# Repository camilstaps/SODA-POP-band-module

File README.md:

# SODA POP band module
This repository contains Eagle files for band modules for the
[SODA POP][sodapop] by [Steve Weber KD1JV][kd1jv]. The SODA POP was originally
designed as a single band QRP CW transceiver on a 3.6" square board. The mods
described below make it a multi-bander.

**Warning**: I have not actually tried to use these files yet. They may have
errors. I shall in no event be liable for any claim, damages or other
liability, whether in action of contract, tort or otherwise, arising from, out
of or in connection with these files or their use.

Two versions are available: one with headers and either through-hole or SMT
components; one with SMT components and a DB9 connector. The DB9 one has an
option for automatic band selection. Some modifications have to be made to the
main board for both modules.

The most recent version of these modules can be ordered from OSH Park from
https://oshpark.com/profiles/PD7LOL.

---

- [Common mods](#common-mods)
- [Through-hole / SMT module with headers](#through-hole--smt-module-with-headers)
- [SMT module with DB9 connector](#smt-module-with-db9-connector)
- [SMT module with DB9 connector and auto band selection](#smt-module-with-db9-connector-and-auto-band-selection)
- [Horizontal format SMT module with DB9 connector and auto band selection](#horizontal-format-smt-module-with-db9-connector-and-auto-band-selection)
- [Author &amp; license](#author--license)

---

## Common mods

### Main board
- The following components are moved to the band module:
	- **TX**: C2, C3, C5 (and C6), C12, L7, L8
	- **RX**: L3, CT1, C31, CT2, L4

	Their values can be taken from the manual under "Band specific parts". One
	part, C31, is on the band module even though it has a fixed value (5p).

### Software
- The software has to be adapted as described in the manual under "Manual band
  selection".

## Through-hole / SMT module With headers
- L3 has to be shorted (on the main board).
- Add 2-pin female headers on the place of L7 and L8
- Add 3-pin female headers on the place of CT1 and CT2 (middle pin should be
  removed)

If you want to make a 160m module with through-hole components, the layout is
slightly different to make room for the T50-2 toroids. Also, C31 is removed in
this case, and L4 is omitted (as in the manual). If building with SMT
components, you can use the same layout as for the other modules, short C31 and
leave out L4.

For 80m, there is no separate layout. Simply leave L4 empty and short C31.

For 60m and 80m, the T37-2 should fit on the normal board.

When plugged in, these band modules cover the ON/OFF switch on the main board.
I would suggest either mounting the switch on the case or omitting it (and turn
the rig on and off by applying and disconnecting a battery or power jack).

## SMT module with DB9 connector
- Add a (male) connector to the main board using short coax cables. The parts
  you should connect are L3, CT2, L7 and L8.

These files show T37-2 toroids, so they should work for all bands except 160m.
The T50-2 toroids for 160m will not fit any more, so they will extend beyond
the board boundaries.

The PCB is placed between the two rows of the DB9 connector.

## SMT module with DB9 connector and auto band selection
This is a very nice mod to the above module, contributed by
[David, VK3IL][vk3il]. It adds a [PCA9536][pca9536] that can be connected to
the I2C pins of the SODA POP controller to add automatic band selection. For
this, the firmware needs to be updated.

## Horizontal format SMT module with DB9 connector and auto band selection
This version is designed to mount parallel and above the main board using a
female DB9 connector on the module. It includes the auto-band selection feature
and is sized to support T30 to T50 size toroids so can be used for 160-10m
bands.

## Author &amp; License
These files were made by [Camil Staps][cs], PD7LOL and [David Giddy][vk3il],
VK3IL. They are hereby placed in the public domain.

[cs]: https://camilstaps.nl
[kd1jv]: http://kd1jv.qrpradio.com/
[pca9536]: http://www.nxp.com/documents/data_sheet/PCA9536.pdf
[sodapop]: https://groups.yahoo.com/neo/groups/AT_Sprint/files/SODA%20POP/
[vk3il]: http://www.vk3il.net/

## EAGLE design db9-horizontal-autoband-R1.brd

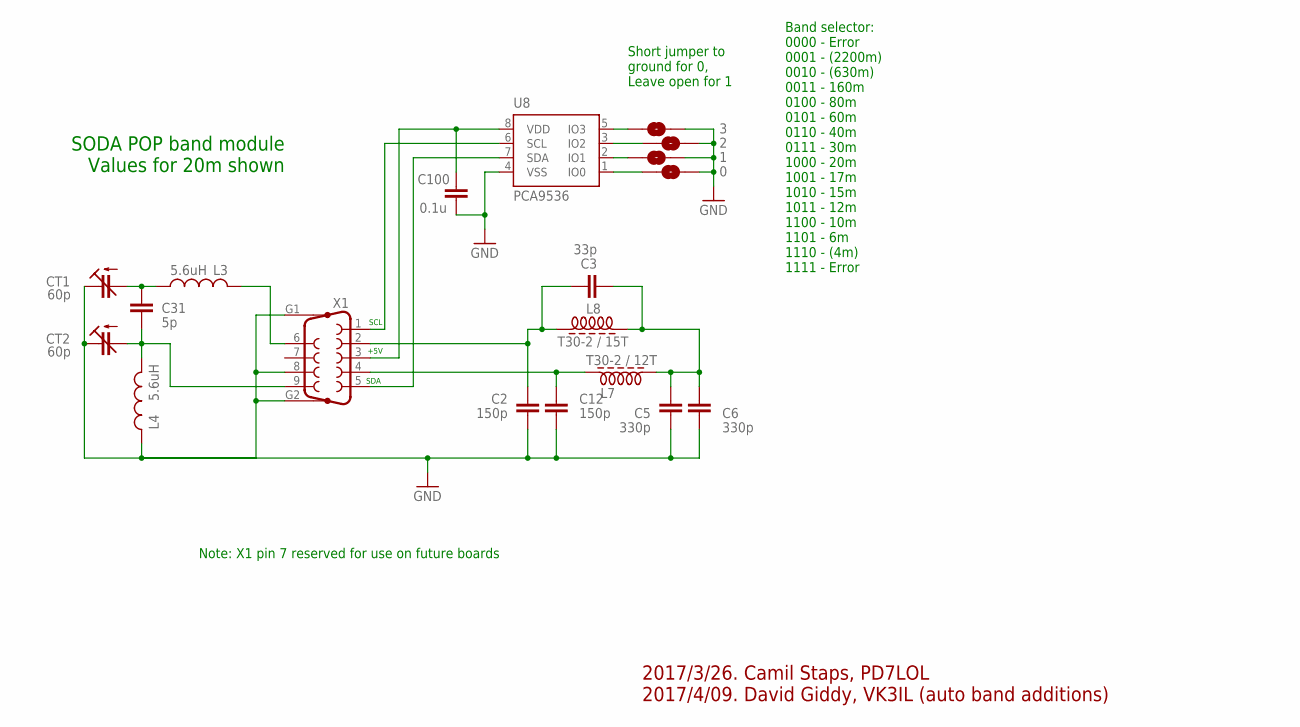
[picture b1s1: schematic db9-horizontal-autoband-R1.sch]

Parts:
0, 1, 2, 3: SJ
C2, C12: 150p; C1206K
C3: 33p; C1206K
C5, C6: 330p; C1206K
C31: 5p; C0805K
C100: 0.1u; C0805K
CT1, CT2: 60p; CTRIMTZ03
L3, L4: 5.6uH; L2012C
L7: T30-2 / 12T; T30-2-28AWG-15T
L8: T30-2 / 15T; T30-2-28AWG-15T
U8: PCA9536; SO8
X1: F09VP

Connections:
GND: 0.2, 1.2, 2.2, 3.2, C2.2, C5.2, C6.2, C12.2, C100.2, CT1.1 (E), CT2.1 (E), L4.2, U8.4 (VSS), X1.8, X1.G1, X1.G2
unnamed: C31.2, CT2.2 (A), L4.1, X1.9
unnamed: C31.1, CT1.2 (A), L3.2
unnamed: L3.1, X1.6
unnamed: C3.2, C5.1, C6.1, L7.P$2 (2), L8.P$2 (2)
unnamed: C12.1, L7.P$1 (1), X1.4
unnamed: C100.1, U8.8 (VDD), X1.3
unnamed: U8.6 (SCL), X1.1
unnamed: U8.7 (SDA), X1.5
unnamed: 3.1, U8.5 (IO3)
unnamed: 2.1, U8.3 (IO2)
unnamed: 1.1, U8.2 (IO1)
unnamed: 0.1, U8.1 (IO0)
unnamed: C2.1, C3.1, L8.P$1 (1), X1.2

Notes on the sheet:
SODA POP band module Values for 20m shown
2017/3/26. Camil Staps, PD7LOL 2017/4/09. David Giddy, VK3IL (auto band additions)
Band selector: 0000 - Error 0001 - (2200m) 0010 - (630m) 0011 - 160m 0100 - 80m 0101 - 60m 0110 - 40m 0111 - 30m 1000 - 20m 1001 - 17m 1010 - 15m 1011 - 12m 1100 - 10m 1101 - 6m 1110 - (4m) 1111 - Error
Short jumper to ground for 0, Leave open for 1
+5V
SCL
SDA
Note: X1 pin 7 reserved for use on future boards

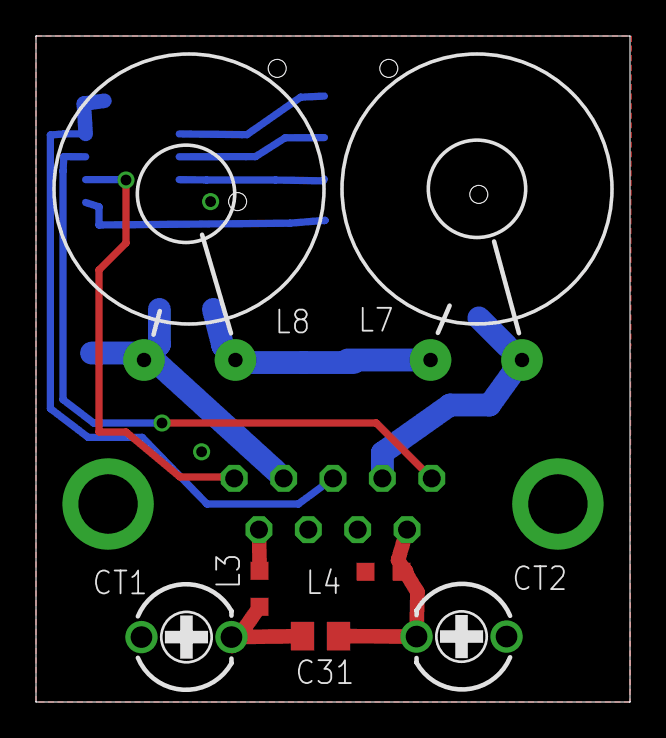
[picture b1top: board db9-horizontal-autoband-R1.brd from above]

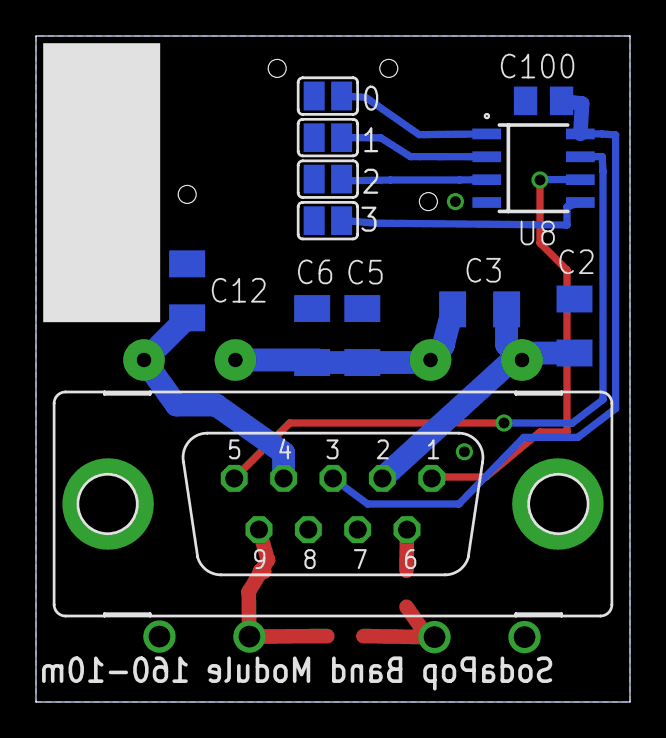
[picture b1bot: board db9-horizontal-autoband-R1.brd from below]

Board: 2 copper layers, 33.0 x 37.0 mm, 19 parts (12 on the bottom side), 14 nets.

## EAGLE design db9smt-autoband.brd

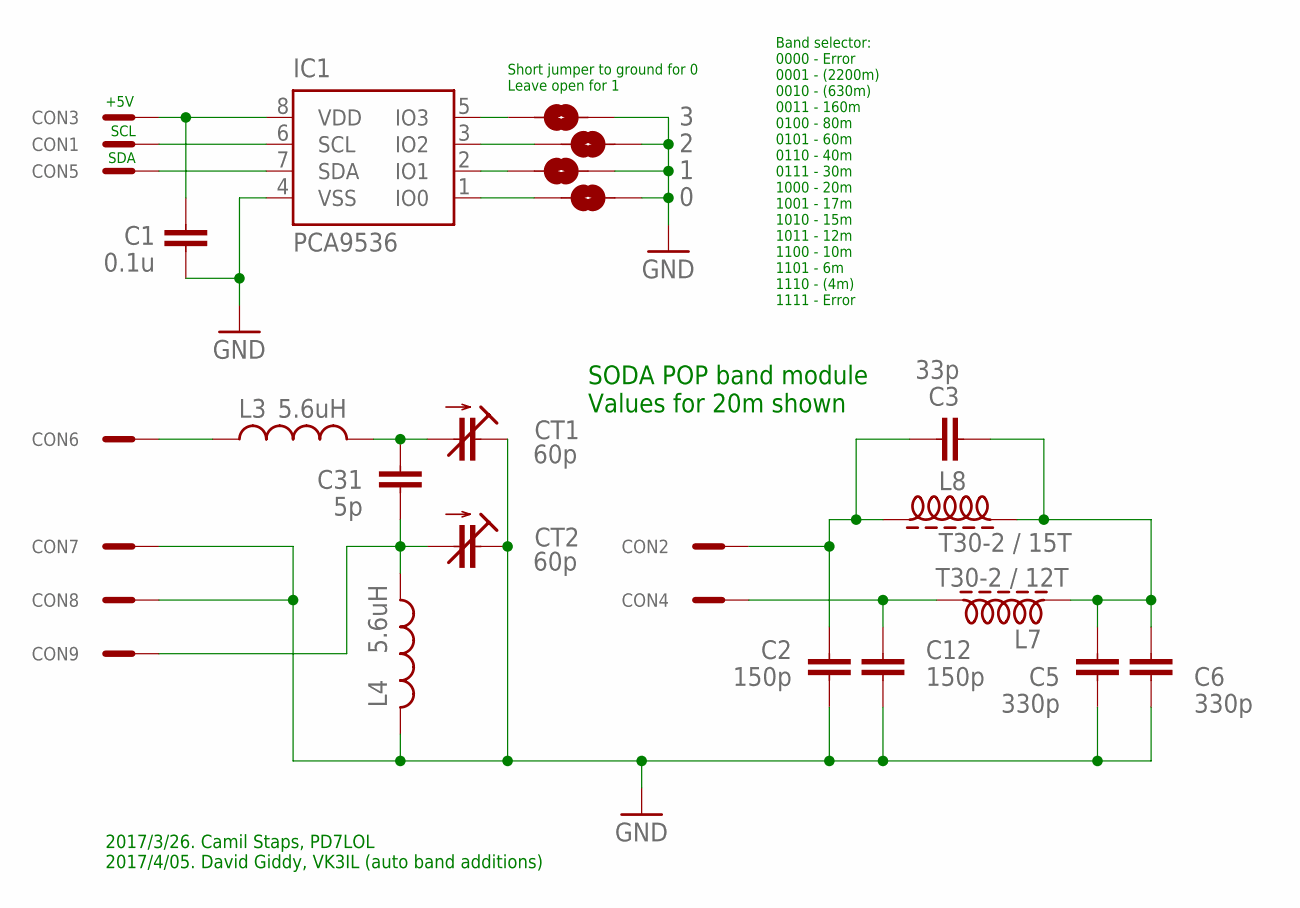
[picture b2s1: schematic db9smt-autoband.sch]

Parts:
0, 1, 2, 3: SJ
C1: 0.1u; C0603
C2, C12: 150p; C0603
C3: 33p; C0603
C5, C6: 330p; C0603
C31: 5p; C0603
CON1, CON2, CON3, CON4, CON5, CON6, CON7, CON8, CON9: PADONPRINT; PAD
CT1, CT2: 60p; CTRIMTZ03
IC1: PCA9536; SO8
L3, L4: 5.6uH; L2012C
L7: T30-2 / 12T; T30-2-28AWG-15T
L8: T30-2 / 15T; T30-2-28AWG-15T

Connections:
GND: 0.2, 1.2, 2.2, 3.2, C1.2, C2.2, C5.2, C6.2, C12.2, CON7.P$1, CON8.P$1, CT1.1 (E), CT2.1 (E), IC1.4 (VSS), L4.2
unnamed: C31.2, CON9.P$1, CT2.2 (A), L4.1
unnamed: C31.1, CT1.2 (A), L3.2
unnamed: CON6.P$1, L3.1
unnamed: C2.1, C3.1, CON2.P$1, L8.P$1 (1)
unnamed: C12.1, CON4.P$1, L7.P$2 (2)
unnamed: C3.2, C5.1, C6.1, L7.P$1 (1), L8.P$2 (2)
unnamed: C1.1, CON3.P$1, IC1.8 (VDD)
unnamed: CON1.P$1, IC1.6 (SCL)
unnamed: CON5.P$1, IC1.7 (SDA)
unnamed: 3.1, IC1.5 (IO3)
unnamed: 2.1, IC1.3 (IO2)
unnamed: 1.1, IC1.2 (IO1)
unnamed: 0.1, IC1.1 (IO0)

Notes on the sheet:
SODA POP band module Values for 20m shown
2017/3/26. Camil Staps, PD7LOL 2017/4/05. David Giddy, VK3IL (auto band additions)
Band selector: 0000 - Error 0001 - (2200m) 0010 - (630m) 0011 - 160m 0100 - 80m 0101 - 60m 0110 - 40m 0111 - 30m 1000 - 20m 1001 - 17m 1010 - 15m 1011 - 12m 1100 - 10m 1101 - 6m 1110 - (4m) 1111 - Error
Short jumper to ground for 0 Leave open for 1
+5V
SCL
SDA

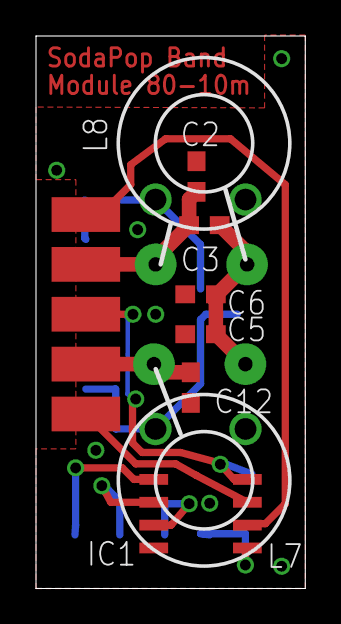
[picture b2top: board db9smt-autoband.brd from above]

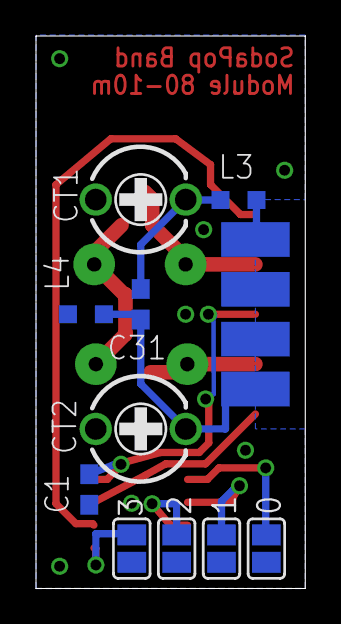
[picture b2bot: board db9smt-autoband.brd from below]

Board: 2 copper layers, 15.0 x 30.7 mm, 27 parts (14 on the bottom side), 14 nets.

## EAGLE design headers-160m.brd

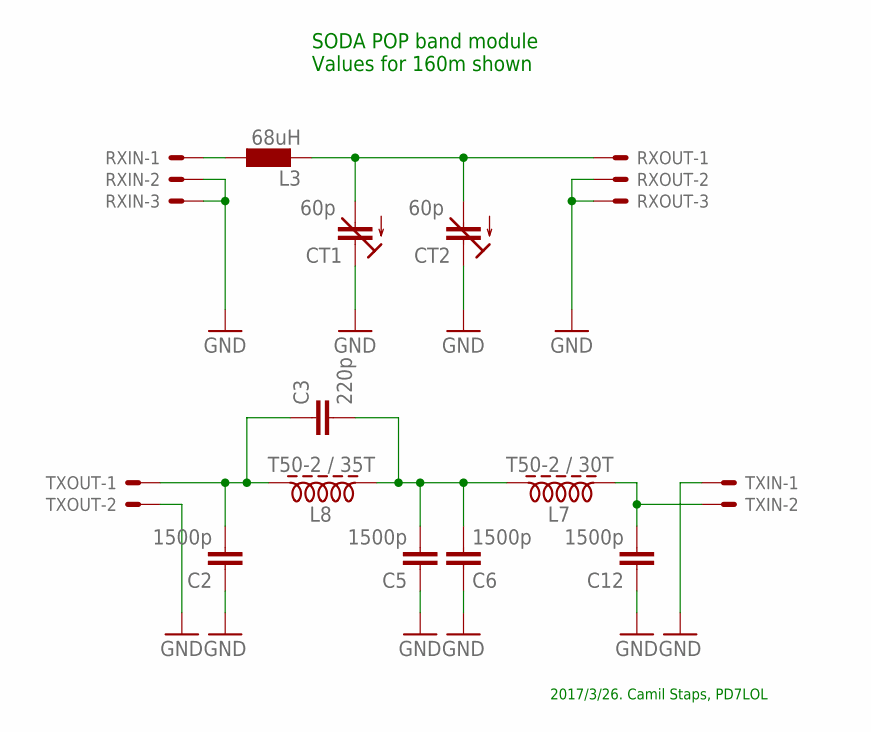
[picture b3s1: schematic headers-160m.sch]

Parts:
C2, C5, C6, C12: 1500p; C5B2.5
C3: 220p; C5B2.5
CT1, CT2: 60p; CTRIMTZ03
L3: 68uH; 0207/10
L7: T50-2 / 30T; T30-2-28AWG-15T
L8: T50-2 / 35T; T30-2-28AWG-15T
RXIN: 22-23-2031
RXOUT: 22-23-2031
TXIN: 22-23-2021
TXOUT: 22-23-2021

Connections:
GND: C2.1, C5.1, C6.1, C12.1, CT1.1 (E), CT2.1 (E), RXIN.2, RXIN.3, RXOUT.2, RXOUT.3, TXIN.1, TXOUT.2
unnamed: L3.1, RXIN.1
unnamed: CT1.2 (A), CT2.2 (A), L3.2, RXOUT.1
unnamed: C3.2, C5.2, C6.2, L7.P$2 (2), L8.P$1 (1)
unnamed: C12.2, L7.P$1 (1), TXIN.2
unnamed: C2.2, C3.1, L8.P$2 (2), TXOUT.1

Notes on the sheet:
SODA POP band module Values for 160m shown
2017/3/26. Camil Staps, PD7LOL

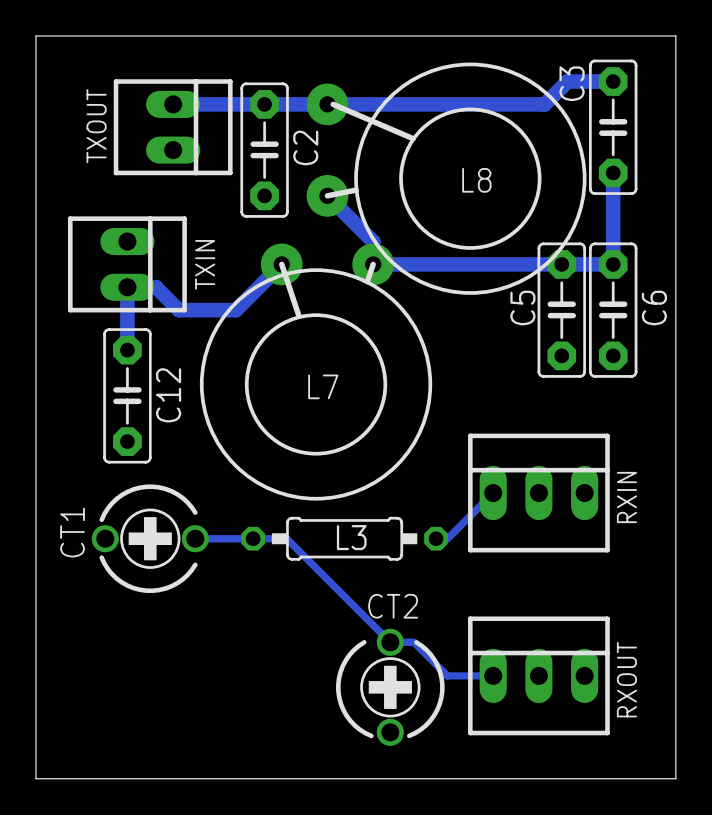
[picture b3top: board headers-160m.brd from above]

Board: 2 copper layers, 35.5 x 41.3 mm, 14 parts (0 on the bottom side), 6 nets.

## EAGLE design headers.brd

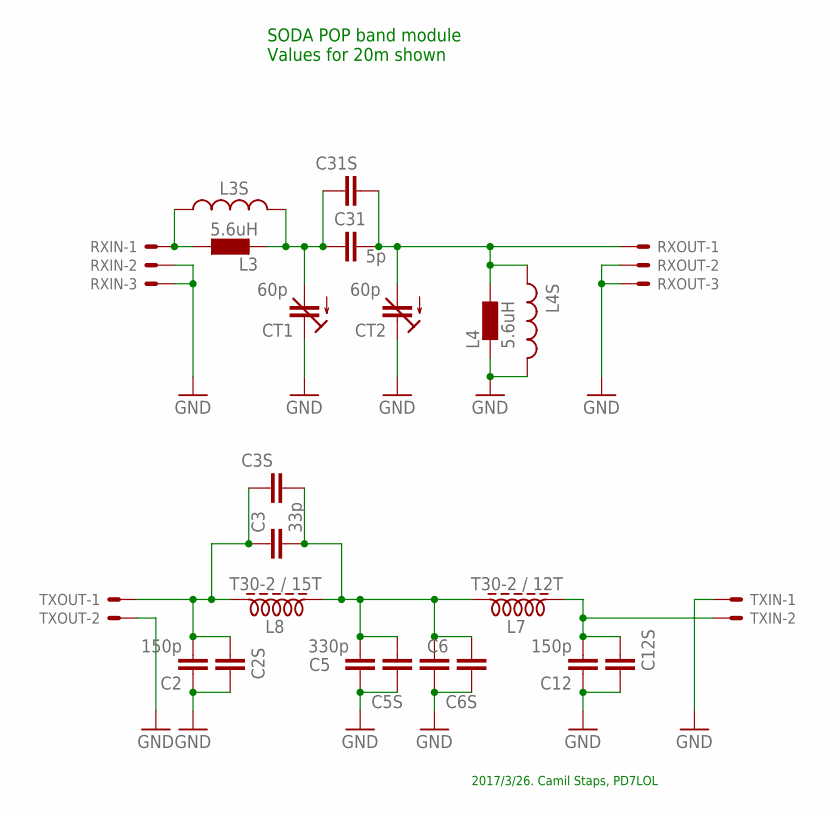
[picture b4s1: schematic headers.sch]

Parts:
C2, C12: 150p; C5B2.5
C2S, C3S, C5S, C6S, C12S, C31S: CC0603; C0603
C3: 33p; C5B2.5
C5, C6: 330p; C5B2.5
C31: 5p; C5B2.5
CT1, CT2: 60p; CTRIMTZ03
L3, L4: 5.6uH; 0207/10
L3S, L4S: L-USL2012C; L2012C
L7: T30-2 / 12T; T30-2-28AWG-15T
L8: T30-2 / 15T; T30-2-28AWG-15T
RXIN: 22-23-2031
RXOUT: 22-23-2031
TXIN: 22-23-2021
TXOUT: 22-23-2021

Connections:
GND: C2.1, C2S.2, C5.1, C5S.2, C6.1, C6S.2, C12.1, C12S.2, CT1.1 (E), CT2.1 (E), L4.2, L4S.2, RXIN.2, RXIN.3, RXOUT.2, RXOUT.3, TXIN.1, TXOUT.2
unnamed: L3.1, L3S.1, RXIN.1
unnamed: C31.1, C31S.1, CT1.2 (A), L3.2, L3S.2
unnamed: C31.2, C31S.2, CT2.2 (A), L4.1, L4S.1, RXOUT.1
unnamed: C3.2, C3S.2, C5.2, C5S.1, C6.2, C6S.1, L7.P$2 (2), L8.P$1 (1)
unnamed: C12.2, C12S.1, L7.P$1 (1), TXIN.2
unnamed: C2.2, C2S.1, C3.1, C3S.1, L8.P$2 (2), TXOUT.1

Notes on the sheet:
SODA POP band module Values for 20m shown
2017/3/26. Camil Staps, PD7LOL

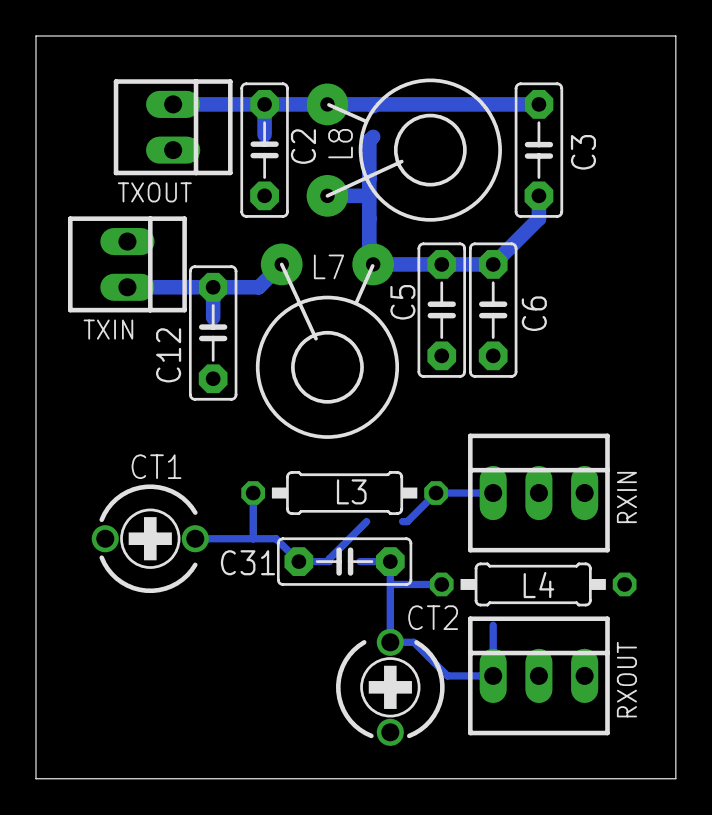
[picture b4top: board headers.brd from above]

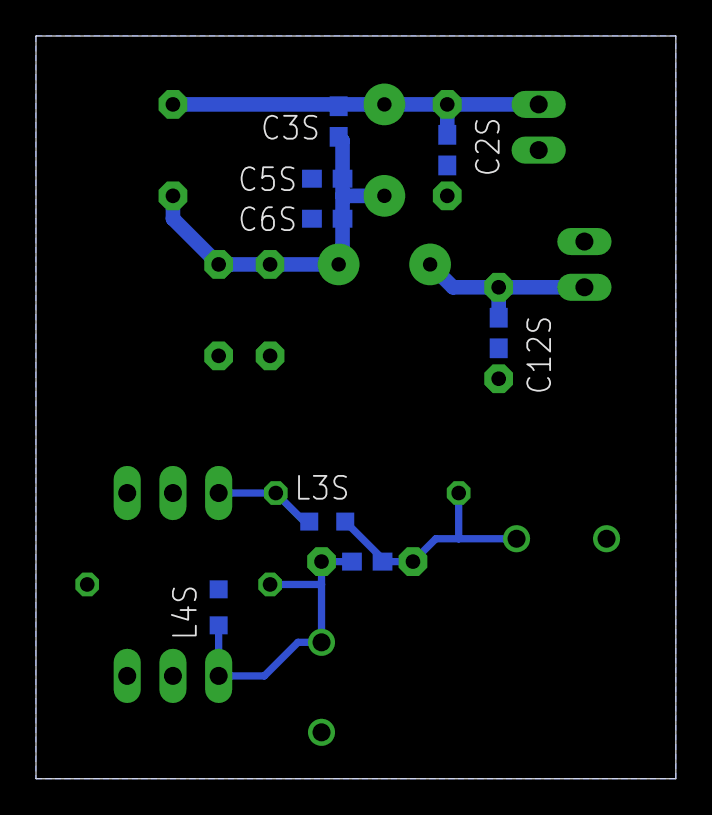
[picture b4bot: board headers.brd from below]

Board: 2 copper layers, 35.5 x 41.3 mm, 24 parts (8 on the bottom side), 7 nets.

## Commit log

2017-03-26 Initial version
2017-03-26 Make board smaller
2017-03-26 Readme, made more space for toroids
2017-03-26 Add gerber file
2017-03-26 Add warning and note about on off switch
2017-03-26 Note about large toroids
2017-03-27 Move labels, add white rectangle for band
2017-03-27 Split up C5-6
2017-03-27 Move RX around for larger board note rectangle
2017-03-27 Move labels
2017-03-28 Move L7 and L8 for more space; change artwork
2017-03-28 Remove gerber
2017-03-28 Change toroid style
2017-03-28 Add separate 160m module
2017-03-28 Fix polygon
2017-03-28 Made traces shorter
2017-03-28 SMT/DB9 version
2017-03-28 Rename bandmodule -> headers
2017-03-28 Add note space on silk screen for db9smt
2017-03-28 Increase trace width to make manufactering easier
2017-03-28 Move bottom band note; OSHPark design rules
2017-03-28 Smaller board
2017-03-28 Nicer bottom silk screen
2017-03-28 GND between signals, remove note space on backside
2017-03-28 Removed right angle
2017-03-30 Headers: split C5-6 again, make some TX traces shorter
2017-03-30 Make DB9 horizontal for smaller footprint and shorter traces
2017-03-30 Move TX lines on DB9 connector
2017-03-30 Note about OSH Park
2017-03-30 Minor fix DB9SMT
2017-04-04 Automatic band selection on the DB9SMT modules (thanks VK3IL)
2017-04-05 SMT components on the header module
2017-04-05 Move SMT components to bottom
2017-04-09 Added DB9 horizontal format files
    Added in a horizontal mount version of the DB9 module. Includes autoband
    capability. TX side capacitors upsized to 1206. Receive capacitor
    upsized to 0805.
2017-04-09 Updated to add references to Horizontal DB9 option
2017-04-09 Resized images
2017-04-10 Adjusted the hole size for the larger toroid pads to 0.9mm
    Adjusted the hole size to allow use of 0.8mm enamelled copper wire for
    the larger toroids. Larger wire provides better rigidity and marginally
    lower loss.
2017-04-13 Fixed hole size on trimmer cap
    Fixed hole size on trimmer cap in library PCA9536.lbr and updated the
    two autoband boards to use the corrected package. Package can be
    replaced on other boards with the one in this library to fix the
    problem. Also moved the text on the horizontal board to the bPlace
    layer. Couldn't do this on the smaller board as no where to put it!
2017-04-25 Fixed errors on horizontal autoband module
    Errors fixed:
    - Disconnected DB9 pin 7 to allow for future use
    - Added 1mm holes to allow toroids to be tied down
    - Moved solder jumpers to make room forholes
    - Fixed board title text so that it will actually print
    - Adjusted restrict on board edge to be narrower
2017-04-25 Updated Readme.md for new image files
